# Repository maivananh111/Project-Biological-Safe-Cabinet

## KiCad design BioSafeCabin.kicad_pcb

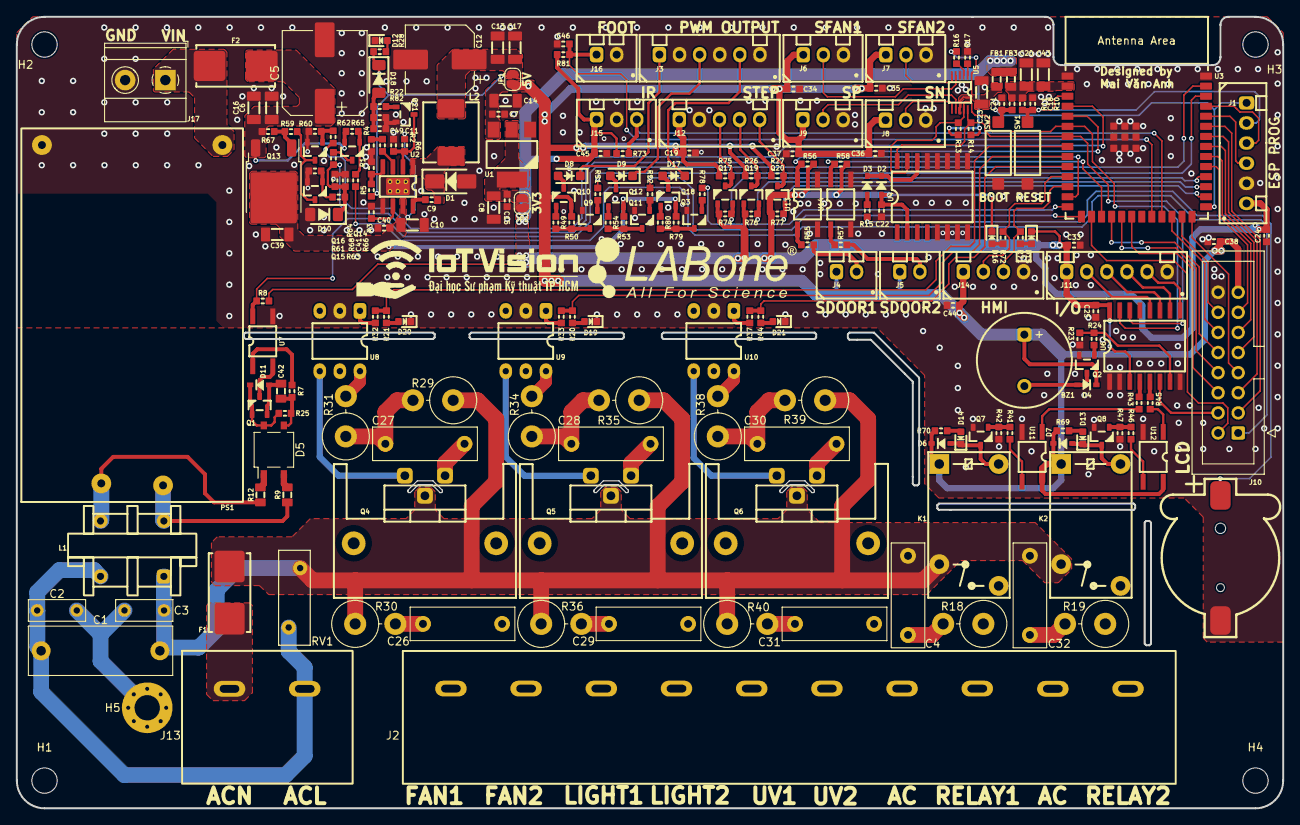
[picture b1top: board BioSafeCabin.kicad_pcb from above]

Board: 2 copper layers, 160.0 x 100.0 mm, 222 parts (0 on the bottom side), 154 nets.

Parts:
BT1: CR1220; BatteryHolder-SMD-CR1220
BZ1: Buzzer; Buzzer_1209
C1: 100nF/275V; C_Rect_L18.0mm_W6.0mm_P15.00mm_FKS3_FKP3
C2, C3: 2.2nF/1KV; C_Disc_D7.0mm_W2.5mm_P5.00mm
C4, C32: 100nF/275V; C_Rect_L13.0mm_W4.0mm_P10.00mm_FKS3_FKP3_MKS4
C5: 470uF; CP_Elec_10x10.5
C6, C13, C43: 100nF; C_1206
C7, C9, C15, C18, C40, C41, C49: 100nF; C_0603
C8, C14, C16, C17, C20, C23, C39: 10uF; C_1206
C10: 1uF; C_1206
C11: 220pF; C_0603
C12: 220uF; CP_Elec_8x10.5
C19, C25, C33, C38, C44, C46: 10uF; C_0603
C21: 10nF; C_0603
C22, C24, C34, C35, C36, C37, C45: 1uF; C_0603
C26, C29, C31: 10nF/275V; C_Rect_L13.0mm_W4.0mm_P10.00mm_FKS3_FKP3_MKS4
C27, C28, C30: 47nF/275V; C_Rect_L13.0mm_W4.0mm_P10.00mm_FKS3_FKP3_MKS4
C42: 10uF; C_0805
D1: SS34; D_SMA
D2, D3, D4, D6, D7, D11: 1N4148WS; D_SOD-323
D5: MB6S; TO-269AA
D8, D9, D17: 1N5819WS; SOD-123F
D10: Z3V3; D_MiniMELF
D12, D13, D14, D19, D20, D21: LED; LED_0603
D15: LED_RX; LED_0603
D16: LED_TX; LED_0603
D18: Z5V; D_MiniMELF
F1, F2: Fuse; F_1808
FB1: FerriteBead_Small; L_0805
FB3: 30/100MHz; L_0805
H1, H2, H3, H4: Hole; MountingHole_3.2mm_M3
H5: Hole_Earth; MountingHole_3.2mm_M3_Pad_Via
J1: ESP_Prog; XH_6P_2.54mm_Vertical
J2: LOAD; TerminalBlock_Screw_HB9500_10P_P9.5mm
J3: PWM OUT; XH_6P_2.54mm_Vertical
J4: DOOR1; XH_2P_2.54mm_Vertical
J5: DOOR2; XH_2P_2.54mm_Vertical
J6: FAN1; XH_3P_2.54mm_Vertical
J7: FAN2; XH_3P_2.54mm_Vertical
J8: P; XH_3P_2.54mm_Vertical
J9: N; XH_3P_2.54mm_Vertical
J10: LCD_KEY; IDC-Header_2x08_P2.54mm_Vertical
J11: IO; XH_6P_2.54mm_Vertical
J12: STEP; XH_5P_2.54mm_Vertical
J13: POWER; TerminalBlock_Screw_HB9500_2P_P9.5mm
J14: HMI; XH_4P_2.54mm_Vertical
J15: IR Sensor; XH_3P_2.54mm_Vertical
J16: FOOT_SWITCH; XH_2P_2.54mm_Vertical
J17: DC IN; TerminalBlock_Phoenix_MKDS-1,5-2-5.08_1x02_P5.08mm_Horizont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
JP1: 5VSW; SolderJumper-2_P1.3mm_Open_RoundedPad1.0x1.5mm
JP2: 3V3SW; SolderJumper-2_P1.3mm_Open_RoundedPad1.0x1.5mm
K1, K2: HF32F-G-005-HS
L1: 10mH; ACFilterChoke_UU9.8
L2: 10uH; L_0630
PS1: HLK-10Mxx; HLK_10Mxx
Q1, Q15, Q16, Q21: S8050; SOT23-3
Q2, Q3, Q7, Q8, Q9, Q11, Q17, Q19, Q20: SI2302; SOT23-3
Q4, Q5, Q6: BTA16-600B; TO-220-3_Vertical_HeatSink
Q10, Q12, Q18: SI2301; SOT23-3
Q13: APM4015P; TO-252-2
Q14: S8550; SOT23-3
R1, R25: 22K; R_0603
R2, R3, R4, R6: 100K; R_0603
R5: 120K; R_0603
R7, R22, R59: 1K; R_0603
R8, R10, R11, R23, R42, R47, R56, R58, R60, R61, R64, R65, R67, R73, R81, R82: 10K; R_0603
R9, R12: 47K/1W; R_0805
R13, R14, R16, R17, R26, R27, R50, R53, R68, R74, R75, R76, R77, R79: 4K7; R_0603
R15, R24, R32, R33, R37, R41, R43, R45, R46, R49, R51, R52, R54, R78, R80: 100; R_0603
R18, R19: 22/2W; R_Axial_DIN0614_L14.3mm_D5.7mm_P5.08mm_Vertical
R20, R21, R28, R44, R55, R57, R62, R63, R66, R69, R70, R71, R72: 470; R_0603
R29, R35, R39: 470/2W; R_Axial_DIN0614_L14.3mm_D5.7mm_P5.08mm_Vertical
R30, R36, R40: 56/2W; R_Axial_DIN0614_L14.3mm_D5.7mm_P5.08mm_Vertical
R31, R34, R38: 330/2W; R_Axial_DIN0614_L14.3mm_D5.7mm_P5.08mm_Vertical
RV1: 10D561K; RV_Disc_D12mm_W4mm_P7.5mm
SW1: RST; SW_SPST_CK
SW2: BOOT; SW_SPST_CK
U1: LD1117-3.3; SOT-223
U2: MP1584EN; SOIC-8_PAD_VIAS
U3: ESP32-S3-WROOM-1-N16; ESP32-S3-WROOM-1
U4: DS3231M; SOIC-16
U5: ADS1115IDGS; TSSOP-10_3x3mm_P0.5mm
U6: PCF8574; SOIC-16
U7, U11, U12, U13, U14: EL357N; SO-4_4.4x3.6_P2.54
U8, U9, U10: MOC3021M; DIP-6_W7.62mm

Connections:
+3V3: C22.1, C24.1, C25.1, C33.1, C45.1, D2.2 (A), D15.1 (K), D16.1 (K), FB1.1, FB3.1, J1.6, J11.1, J15.1, JP2.2 (B), Q17.1 (G), Q19.1 (G), Q20.1 (G), R8.2, R13.1, R14.1, R56.2, R58.2, R73.2, R74.1, R76.1, R77.1, R81.2, U4.2 (VCC), U6.3 (A2), U6.16 (VDD)
+5V: BZ1.1 (-), C7.1, C14.1, C19.1, C34.1, C35.1, C36.1, C37.1, C38.1, C44.1, D4.1 (K), D6.1 (K), D7.1 (K), J4.1, J5.1, J6.1, J7.1, J8.1, J9.1, J10.15, J12.1, J14.1, JP1.2 (B), K1.1, K2.1, Q10.2 (S), R26.1, R27.1, R50.2, R69.2, R70.2, R75.1, U1.3 (VI), U11.4, U12.4
+12V: C10.2, C39.1, C40.1, Q12.2 (S), Q13.2 (D), Q18.2 (S), R6.1, R53.2, R79.2, U2.7 (VIN)
/LOAD_CONTROL/ACDET: R8.1, U3.39 (IO1), U7.4
/LOAD_CONTROL/BUZZER: R23.1, R24.2, U6.7 (P3)
/LOAD_CONTROL/DEV1: J2.8, K1.5, R18.1
/LOAD_CONTROL/DEV2: J2.10, K2.5, R19.1
/LOAD_CONTROL/EXIO1: J11.5, U6.9 (P4)
/LOAD_CONTROL/EXIO2: J11.4, U6.10 (P5)
/LOAD_CONTROL/EXIO3: J11.3, U6.11 (P6)
/LOAD_CONTROL/EXIO4: J11.2, U6.12 (P7)
/LOAD_CONTROL/FAN: R21.2, R32.2, U3.8 (IO15)
/LOAD_CONTROL/LED: J10.4, U6.6 (P2)
/LOAD_CONTROL/LIGHT: R20.2, R33.2, U3.9 (IO16)
/LOAD_CONTROL/LOAD_FAN: C26.2, C27.2, J2.2, Q4.1 (A1)
/LOAD_CONTROL/LOAD_LIGHT: C28.2, C29.2, J2.4, Q5.1 (A1)
/LOAD_CONTROL/LOAD_UV: C30.2, C31.2, J2.6, Q6.1 (A1)
/LOAD_CONTROL/PWM1: R51.1, U3.38 (IO2)
/LOAD_CONTROL/PWM2: R52.1, U3.15 (IO3)
/LOAD_CONTROL/PWM3: R78.1, U3.14 (IO20)
/LOAD_CONTROL/PWMOUT1: D8.1 (K), J3.1
/LOAD_CONTROL/PWMOUT2: D9.1 (K), J3.3
/LOAD_CONTROL/PWMOUT3: D17.1 (K), J3.5
/LOAD_CONTROL/RELAY1: R43.2, U6.4 (P0)
/LOAD_CONTROL/RELAY2: R45.2, U6.5 (P1)
/LOAD_CONTROL/SCL: R14.2, U3.7 (IO7), U4.16 (SCL), U5.10 (SCL), U6.14 (SCL)
/LOAD_CONTROL/SDA: R13.2, U3.6 (IO6), U4.15 (SDA), U5.9 (SDA), U6.15 (SDA)
/LOAD_CONTROL/UV: R37.2, R44.2, U3.10 (IO17)
/MCU/BOOT: C21.1, J1.1, R11.2, SW2.2, U3.27 (IO0)
/MCU/BUTTON_POWER: J10.1, R66.2
/MCU/DOOR1: R56.1, U3.13 (IO19), U13.4
/MCU/DOOR2: R58.1, U3.17 (IO9), U14.4
/MCU/FOOT_SWITCH: C46.1, J16.1, R81.1, U3.22 (IO14)
/MCU/POWER_DETECT: C41.1, D10.1 (K), R63.1, R64.2, R68.2, U3.5 (IO5)
/MCU/POWER_ENABLE: R62.2, U3.4 (IO4)
/MCU/RESET: C18.1, J1.2, R10.2, SW1.2, U3.3 (EN)
/POWER/3V3_TEST: C8.1, C15.1, JP2.1 (A), U1.2 (VO)
/POWER/5V_TEST: C12.1, C13.1, C17.1, D18.1 (K), JP1.1 (A), L2.2, R5.1, R28.2
/SENSOR_RTC/SENSOR_DOOR1: J4.2, R55.1
/SENSOR_RTC/SENSOR_DOOR2: J5.2, R57.1
/SENSOR_RTC/SENSOR_FAN1: J6.2, U5.4 (AIN0)
/SENSOR_RTC/SENSOR_FAN2: J7.2, U5.5 (AIN1)
/SENSOR_RTC/SENSOR_N: J9.2, U5.7 (AIN3)
/SENSOR_RTC/SENSOR_P: J8.2, U5.6 (AIN2)
ACL: C1.1, C2.1, J2.1, J2.3, J2.5, J2.7, J2.9, J13.2, L1.4, RV1.1
ACN: F1.1, J13.1
AC_AF: C1.2, C3.2, C4.2, C32.2, F1.2, K1.3, K2.3, L1.1, Q4.2 (A2), Q5.2 (A2), Q6.2 (A2), R29.1, R30.1, R35.1, R36.1, R39.1, R40.1, RV1.2
AC_AFL: L1.3, PS1.1 (AC1), R12.1
AC_AFN: L1.2, PS1.2 (AC2), R9.1
BUTTON1: J10.3, U3.35 (IO42)
BUTTON2: J10.5, U3.34 (IO41)
BUTTON3: J10.7, U3.26 (IO45)
BUTTON_BACK: J10.12, U3.24 (IO47)
BUTTON_SETTING: J10.14, U3.25 (IO48)
BUTTON_START: J10.2, U3.16 (IO46)
ENCODER_A: J10.11, U3.32 (IO39)
ENCODER_B: J10.13, U3.31 (IO38)
ENCODER_W: J10.9, U3.33 (IO40)
Earth: C2.2, C3.1, H5.1
GND: BT1.2 (-), C5.2, C6.2, C7.2, C8.2, C10.1, C12.2, C13.2, C14.2, C15.2, C16.2, C17.2, C18.2, C19.2, C20.2, C21.2, C22.2, C23.2, C24.2, C25.2, C33.2, C34.2, C35.2, C36.2, C37.2, C38.2, C39.2, C40.2, C41.2, C43.2, C44.2, C45.2, C46.2, C49.2, D1.2, D10.2 (A), D12.1 (K), D19.1 (K), D20.1 (K), D21.1 (K), J1.5, J3.2, J3.4, J3.6, J6.3, J7.3, J8.3, J9.3, J10.16, J11.6, J12.2, J14.4, J15.2, J16.2, J17.2, PS1.4 (VO-), Q2.2 (S), Q3.2 (S), Q7.2 (S), Q8.2 (S), Q9.2 (S), Q11.2 (S), Q15.2 (E), Q16.2 (E), Q21.2 (E), R1.1, R2.1, R3.1, R4.1, R17.2, R23.2, R42.2, R47.2, R60.2, R61.2, R68.1, R82.1, SW1.1, SW2.1, U1.1 (GND), U2.5 (GND), U2.9 (EP), U3.1 (GND), U3.40 (GND), U3.41_1 (GND), U3.41_2 (GND), U3.41_3 (GND), U3.41_4 (GND), U3.41_5 (GND), U3.41_6 (GND), U3.41_7 (GND), U3.41_8 (GND), U3.41_9 (GND), U4.5 (GND), U4.6 (GND), U4.7 (GND), U4.8 (GND), U4.9 (GND), U4.10 (GND), U4.11 (GND), U4.12 (GND), U4.13 (GND), U5.3 (GND), U6.1 (A0), U6.2 (A1), U6.8 (VSS), U7.3, U8.2, U9.2, U10.2, U11.2, U12.2, U13.2, U13.3, U14.2, U14.3
IR: J15.3, R73.1, U3.23 (IO21)
LCD_EN/CLK: J10.6, U3.20 (IO12)
LCD_RS/CS: J10.10, U3.18 (IO10)
LCD_RW/SDI: J10.8, U3.19 (IO11)
unnamed: BT1.1 (+), R15.2
unnamed: BZ1.2 (+), D4.2 (A), Q2.3 (D)
unnamed: C4.1, R18.2
unnamed: C11.2, R4.2
unnamed: C26.1, R30.2
unnamed: C27.1, R29.2, R31.1
unnamed: C28.1, R34.1, R35.2
unnamed: C29.1, R36.2
unnamed: C30.1, R38.1, R39.2
unnamed: C31.1, R40.2
unnamed: C32.1, R19.2
unnamed: D2.1 (K), D3.1 (K), U4.14 (VBAT)
unnamed: D3.2 (A), R15.1
unnamed: C42.1, D5.3 (+), R7.1, R25.2
unnamed: D5.1, R12.2
unnamed: D5.2, R9.2
unnamed: D8.2 (A), Q10.3 (D)
unnamed: D9.2 (A), Q12.3 (D)
unnamed: C42.2, D11.2 (A), Q1.2 (E)
unnamed: D5.4 (-), D11.1 (K), Q1.1 (B), R25.1
unnamed: D12.2 (A), R28.1
unnamed: D13.2 (A), R69.1
unnamed: D7.2 (A), D13.1 (K), K2.6, Q8.3 (D)
unnamed: D14.2 (A), R70.1
unnamed: D6.2 (A), D14.1 (K), K1.6, Q7.3 (D)
unnamed: D15.2 (A), R71.1
unnamed: D16.2 (A), R72.1
unnamed: D17.2 (A), Q18.3 (D)
unnamed: C49.1, D18.2 (A), R22.1, R82.2
unnamed: D19.2 (A), R20.1
unnamed: D20.2 (A), R21.1
unnamed: D21.2 (A), R44.1
unnamed: J12.3, Q17.3 (D), R75.2
unnamed: J12.4, Q19.3 (D), R26.2
unnamed: J12.5, Q20.3 (D), R27.2
unnamed: F2.1, J17.1, PS1.3 (VO+)
unnamed: Q1.3 (C), U7.2
unnamed: Q2.1 (G), R24.1
unnamed: Q3.3 (D), R79.1, R80.1
unnamed: Q3.1 (G), R78.2
unnamed: Q4.3 (G), U8.4
unnamed: Q5.3 (G), U9.4
unnamed: Q6.3 (G), U10.4
unnamed: Q7.1 (G), R41.1, R42.1
unnamed: Q8.1 (G), R46.1, R47.1
unnamed: Q9.3 (D), R49.1, R50.1
unnamed: Q9.1 (G), R51.2
unnamed: Q10.1 (G), R49.2
unnamed: Q11.3 (D), R53.1, R54.1
unnamed: Q11.1 (G), R52.2
unnamed: Q12.1 (G), R54.2
unnamed: Q13.1 (G), R59.1, R67.1
unnamed: Q14.1 (B), R65.1, R66.1
unnamed: Q14.3 (C), R64.1
unnamed: Q15.1 (B), R61.1, R63.2
unnamed: Q15.3 (C), Q16.3 (C), R59.2
unnamed: Q16.1 (B), R60.1, R62.1
unnamed: Q18.1 (G), R80.2
unnamed: Q21.1 (B), R22.2
unnamed: Q21.3 (C), R2.2, R6.2, U2.2 (EN)
unnamed: R7.2, U7.1
unnamed: R31.2, U8.6
unnamed: R32.1, U8.1
unnamed: R33.1, U9.1
unnamed: R34.2, U9.6
unnamed: R37.1, U10.1
unnamed: R38.2, U10.6
unnamed: R41.2, U11.3
unnamed: R43.1, U11.1
unnamed: R45.1, U12.1
unnamed: R46.2, U12.3
unnamed: R55.2, U13.1
unnamed: R57.2, U14.1
unnamed: C9.1, U2.8 (BST)
unnamed: C11.1, U2.3 (COMP)
unnamed: R1.2, R5.2, U2.4 (FB)
unnamed: R3.2, U2.6 (FREQ)
unnamed: C9.2, D1.1, L2.1, U2.1 (SW)
unnamed: C20.1, C43.1, FB3.2, R10.1, R11.1, U3.2 (3V3)
unnamed: R17.1, U5.1 (ADDR)
unnamed: R16.2, U5.2 (ALERT/RDY)
unnamed: C23.1, FB1.2, R16.1, U5.8 (VDD)
RXD0: J1.4, U3.36 (RXD0)
STEP_DIR: Q19.2 (S), R76.2, U3.29 (IO36)
STEP_EN: Q17.2 (S), R74.2, U3.30 (IO37)
STEP_PUL: Q20.2 (S), R77.2, U3.28 (IO35)
TXD0: J1.3, U3.37 (TXD0)
U1_RX: J14.3, R71.2, U3.12 (IO8)
U1_TX: J14.2, R72.2, U3.11 (IO18)
VCC: C5.1, C6.1, C16.1, F2.2, Q13.3 (S), Q14.2 (E), R65.2, R67.2

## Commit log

2023-09-11 Finished PCB layout.

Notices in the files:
parts and their libraries:
Copyright 2021 Accelerated Designs. All rights reserved.
